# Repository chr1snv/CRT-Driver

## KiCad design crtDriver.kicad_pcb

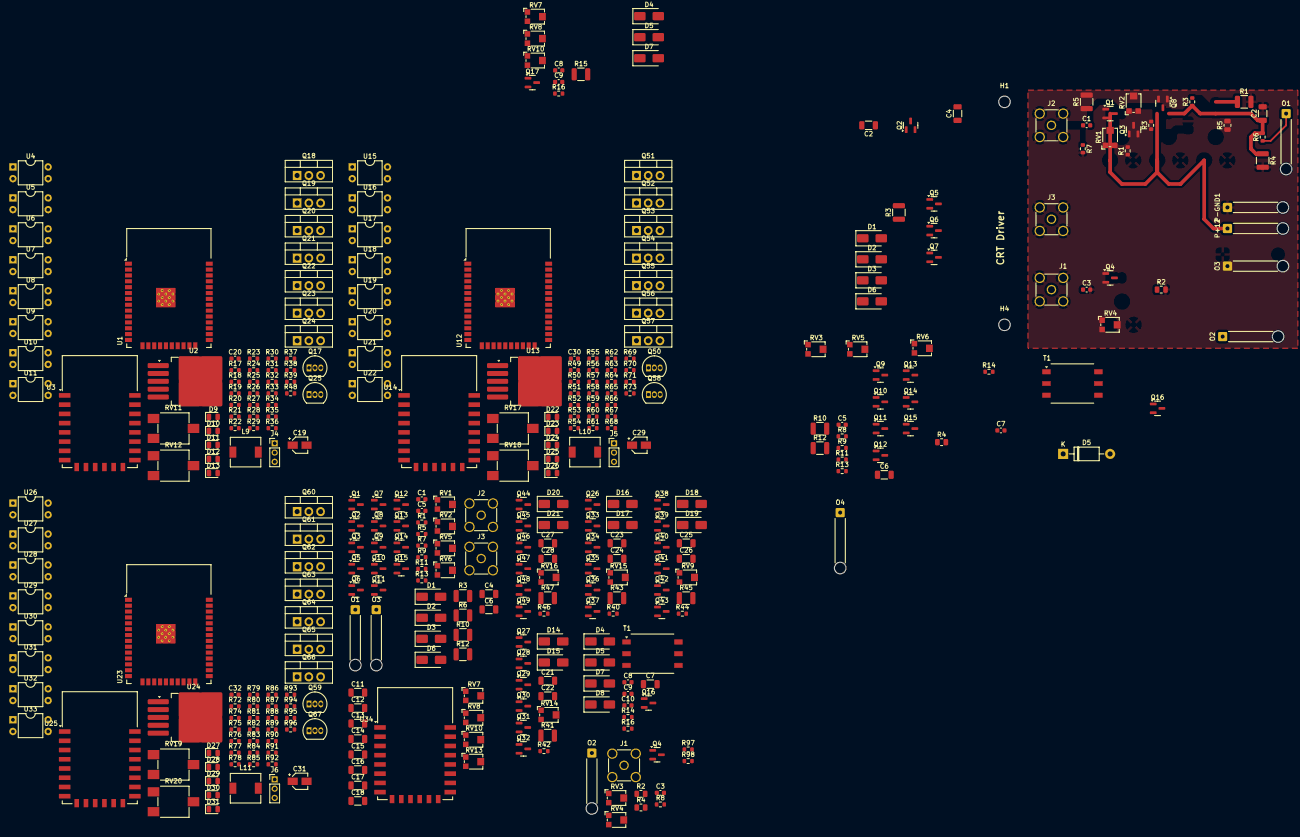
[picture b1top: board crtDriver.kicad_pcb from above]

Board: 2 copper layers, 372 parts (0 on the bottom side), 213 nets.

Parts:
C1, C1#2, C5, C5#2, C8: 4u; C_0603_1608Metric
C2, C4, C4#2, C6, C6#2, C21, C24, C26, C28: 47u; C_1206_3216Metric
C2#2: 2000u; C_1206_3216Metric
C3, C3#2: 100n; C_0603_1608Metric
C7, C8#2, C9#2, C10: 20u; C_0603_1608Metric
C7#2: 1000u; C_1206_3216Metric
C9: 1u; C_0603_1608Metric
C11, C12, C13, C14, C15, C16, C17, C18: 40u; C_1206_3216Metric
C19, C29, C31: 470uF 25V; CP_Elec_3x5.3
C20, C30, C32: 4.7uF 25V; C_0603_1608Metric
C22, C23, C25, C27: 1u; C_1206_3216Metric
D1, D1#2, D2, D2#2, D3, D3#2, D4, D4#2, D5, D5#3, D6, D6#2, D7, D7#2, D8, D14, D15, D16, D17, D18, D19, D20, D21: US1A; D_SMA
D5#2: 1N4007; D_DO-41_SOD81_P10.16mm_Horizontal
D9, D10, D11, D12, D13, D22, D23, D24, D25, D26, D27, D28, D29, D30, D31: 1N4001; D_0805_2012Metric
H1, H2, H3, H4: MountingHole; MountingHole_2.5mm
J1, J1#2: Lum_In; SMA_Amphenol_901-144_Vertical
J2, J2#2: H_Sync; SMA_Amphenol_901-144_Vertical
J3, J3#2: V_Sync; SMA_Amphenol_901-144_Vertical
J4, J5, J6: Conn_01x03_Female; PinHeader_1x03_P2.00mm_Vertical
L9, L10, L11: 9u; L_6.3x6.3_H3
O1, O1#2: H_Ramp_Out; SolderWire-0.25sqmm_1x01_D0.65mm_OD2mm_Relief
O2, O2#2: Lum_Out; SolderWire-0.25sqmm_1x01_D0.65mm_OD2mm_Relief
O3, O3#2, O4: V_Ramp_Out; SolderWire-0.25sqmm_1x01_D0.65mm_OD2mm_Relief
P+12: +12V; SolderWire-0.25sqmm_1x01_D0.65mm_OD2mm_Relief
P-GND1: +12V; SolderWire-0.25sqmm_1x01_D0.65mm_OD2mm_Relief
Q1, Q1#2, Q2, Q2#2, Q3, Q3#2, Q4, Q4#2, Q5, Q5#2, Q6, Q6#2, Q7, Q7#2, Q8, Q8#2, Q9, Q9#2, Q10, Q10#2, Q11, Q11#2, Q12, Q12#2, Q13, Q13#2, Q14, Q14#2, Q15, Q15#2, Q16#2, Q17, Q26, Q27, Q28, Q29, Q30, Q31, Q32, Q33, Q34, Q35, Q36, Q37, Q38, Q39, Q40, Q41, Q42, Q43, Q44, Q45, Q46, Q47, Q48, Q49: 2N7000; SOT-23
Q16: 410N; SOT-23
Q17#2, Q25, Q50, Q58, Q59, Q67: 2N7000; TO-92_Inline
Q18, Q19, Q20, Q21, Q22, Q23, Q24, Q51, Q52, Q53, Q54, Q55, Q56, Q57, Q60, Q61, Q62, Q63, Q64, Q65, Q66: IRF3205; TO-220-3_Vertical
R1, R3#4, R6, R12, R12#2, R41, R43, R45, R47: 10; R_1210_3225Metric
R1#2, R3, R5, R8, R8#2, R11, R11#2, R14, R40, R42, R44, R46: 10000; R_0603_1608Metric
R1#3, R7, R9, R9#2: 1000000; R_0603_1608Metric
R2, R2#2: 100000; R_0805_2012Metric
R3#2: 68; R_0603_1608Metric
R3#3, R5#3, R10, R10#2: 1000; R_1210_3225Metric
R4, R4#2: 100; R_0805_2012Metric
R4#3: 100; R_1210_3225Metric
R5#2: 1000; R_0805_2012Metric
R6#2, R7#2, R13, R13#2: 1000; R_0603_1608Metric
R14#2: 4; R_0603_1608Metric
R15: .5; R_1210_3225Metric
R16: 100000; R_0603_1608Metric
R16#2: .5; R_0603_1608Metric
R17, R24, R26, R27, R28, R29, R30, R39, R49, R56, R58, R59, R60, R61, R62, R71, R74, R81, R83, R84, R85, R86, R87, R96: 1K; R_0603_1608Metric
R18, R19, R20, R21, R22, R23, R50, R51, R52, R53, R54, R55, R75, R76, R77, R78, R79, R80: 200; R_0603_1608Metric
R25, R31, R32, R33, R34, R35, R36, R37, R38, R57, R63, R64, R65, R66, R67, R68, R69, R70, R82, R88, R89, R90, R91, R92, R93, R94, R95: 10K; R_0603_1608Metric
R48, R72, R73: 0; R_0603_1608Metric
R97, R98: 4.7K; R_0603_1608Metric
RV1, RV1#2, RV3#2, RV4, RV5, RV5#2, RV7#2, RV8, RV10#2, RV13: 2M; Potentiometer_Bourns_TC33X_Vertical
RV2, RV2#2, RV9, RV14, RV15, RV16: 250; Potentiometer_Bourns_TC33X_Vertical
RV3, RV4#2, RV7, RV8#2, RV10: 2000; Potentiometer_Bourns_TC33X_Vertical
RV6, RV6#2: 5000; Potentiometer_Bourns_TC33X_Vertical
RV11, RV17, RV19: 50K POT; Potentiometer_ACP_CA6-VSMD_Vertical
RV12, RV18, RV20: 2K POT; Potentiometer_ACP_CA6-VSMD_Vertical
T1: Transformer_1P_1S; Transformer_Wuerth_750315371
T1#2: Wuerth_750315371; Transformer_Wuerth_750315371
U1, U12, U23: ESP32-WROOM-32
U2, U13, U24: LM2576HVS-5; TO-263-5_TabPin3
U3, U14, U25, U34: ESP-12E
U4, U5, U6, U7, U8, U9, U10, U11, U15, U16, U17, U18, U19, U20, U21, U22, U26, U27, U28, U29, U30, U31, U32, U33: PC817; DIP-4_W7.62mm

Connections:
+3.3V: R97.1, R98.1
+5V: R48.2, R72.2, R73.2, RV12.3, RV18.3, RV20.3, U3.8 (VCC), U14.8 (VCC), U25.8 (VCC)
+12V: C2#2.1, C7#2.1, D4.1 (K), D7.1 (K), L9.2, L10.2, L11.2, P+12.1, Q2#2.1 (S), Q5.1 (S), Q8.1 (S), Q8#2.1 (S), Q12.1 (S), Q12#2.1 (S), Q15.1 (S), Q15#2.1 (S), Q19.2 (D), Q21.2 (D), Q23.2 (D), Q30.1 (S), Q32.1 (S), Q34.1 (S), Q37.1 (S), Q40.1 (S), Q43.1 (S), Q46.1 (S), Q49.1 (S), Q52.2 (D), Q54.2 (D), Q56.2 (D), Q61.2 (D), Q63.2 (D), Q65.2 (D), R1#2.1, R2.1, R2#2.1, R3#3.1, R4.1, R4#2.1, R5.1, R5#3.1, R10.1, R10#2.1, R11.1, R11#2.1, R15.2, R40.1, R42.1, R44.1, R46.1, RV1.1, RV1#2.1, RV3#2.1, RV4.1, RV5.1, RV5#2.1, RV10.1, T1.1 (AA), T1#2.1 (AA), U2.1 (VIN), U4.4, U13.1 (VIN), U15.4, U24.1 (VIN), U26.4
+36V: C19.1, C29.1, C31.1, D9.1 (K), D10.1 (K), D11.1 (K), D12.1 (K), D22.1 (K), D23.1 (K), D24.1 (K), D25.1 (K), D27.1 (K), D28.1 (K), D29.1 (K), D30.1 (K), R24.1, R26.1, R27.1, R28.1, R29.1, R30.1, R56.1, R58.1, R59.1, R60.1, R61.1, R62.1, R81.1, R83.1, R84.1, R85.1, R86.1, R87.1, RV11.3, RV17.3, RV19.3
/BLDC_Driver1/A: D23.2 (A), D26.2 (A), J5.1, Q52.3 (S), Q53.2 (D)
/BLDC_Driver1/ADC: R69.2, U14.2 (ADC)
/BLDC_Driver1/B: D24.2 (A), J5.2, Q56.3 (S), Q57.2 (D)
/BLDC_Driver1/C: D25.2 (A), J5.3, Q54.3 (S), Q55.2 (D)
/BLDC_Driver1/Flashing fails if high: U12.24 (IO2), U12.25 (IO0)
/BLDC_Driver2/A: D28.2 (A), D31.2 (A), J6.1, Q61.3 (S), Q62.2 (D)
/BLDC_Driver2/ADC: R94.2, U25.2 (ADC)
/BLDC_Driver2/B: D29.2 (A), J6.2, Q65.3 (S), Q66.2 (D)
/BLDC_Driver2/C: D30.2 (A), J6.3, Q63.3 (S), Q64.2 (D)
/BLDC_Driver2/Flashing fails if high: U23.24 (IO2), U23.25 (IO0)
/BLDC_Driver/A: D10.2 (A), D13.2 (A), J4.1, Q19.3 (S), Q20.2 (D)
/BLDC_Driver/ADC: R37.2, U3.2 (ADC)
/BLDC_Driver/B: D11.2 (A), J4.2, Q23.3 (S), Q24.2 (D)
/BLDC_Driver/C: D12.2 (A), J4.3, Q21.3 (S), Q22.2 (D)
/BLDC_Driver/Flashing fails if high: U1.24 (IO2), U1.25 (IO0)
/BLDC_Driver/SCL: R98.2, U1.22 (SDI/SD1), U12.22 (SDI/SD1), U23.22 (SDI/SD1)
/BLDC_Driver/SDA: R97.2, U1.21 (SDO/SD0), U12.21 (SDO/SD0), U23.21 (SDO/SD0)
/FocusingCoils/PWMAmplifier1/SELECTED_RAMP_OUT: C13.1, C14.1, C24.2, D17.1 (K), Q35.1 (S), RV13.1
/FocusingCoils/PWMAmplifier1/Scaled_Ramp_IN: C23.1, Q26.2 (G), Q34.2 (G), RV13.2
/FocusingCoils/PWMAmplifier2/SELECTED_RAMP_OUT: C15.1, C16.1, C26.2, D19.1 (K), Q41.1 (S), RV8.1
/FocusingCoils/PWMAmplifier2/Scaled_Ramp_IN: C25.1, Q38.2 (G), Q40.2 (G), RV8.2
/FocusingCoils/PWMAmplifier3/SELECTED_RAMP_OUT: C17.1, C18.1, C28.2, D21.1 (K), Q47.1 (S), RV10#2.1
/FocusingCoils/PWMAmplifier3/Scaled_Ramp_IN: C27.1, Q44.2 (G), Q46.2 (G), RV10#2.2
/FocusingCoils/PWMAmplifier/SELECTED_RAMP_OUT: C11.1, C12.1, C21.2, D15.1 (K), Q28.1 (S), RV7#2.1
/FocusingCoils/PWMAmplifier/Scaled_Ramp_IN: C22.1, Q29.2 (G), Q30.2 (G), RV7#2.2
/HighVoltageAndFillamentPower/H_Sync_Toggle: Q2.1 (S), Q7.2 (G), Q8#2.2 (G), Q16.2 (G), R5.2
/HorizontalAndVerticalRamp/H_Ramp_Out: C4.2, D6.1 (K), Q6#2.1 (S), R7#2.2
/HorizontalAndVerticalRamp/H_Sync: C1#2.1, J2.1 (In), R1#3.1
/HorizontalAndVerticalRamp/Inverted_H_Sync: Q1#2.1 (S), Q2.2 (G), Q5.2 (G), R3#3.2
/HorizontalAndVerticalRamp/Inverted_V_Sync: Q9#2.1 (S), Q10#2.2 (G), Q12#2.2 (G), R10.2
/HorizontalAndVerticalRamp/Positive_V_Sync: Q10#2.1 (S), Q14#2.2 (G), Q15#2.2 (G), R11.2
/HorizontalAndVerticalRamp/V_Ramp_Out: C6#2.2, D3.1 (K), Q13.1 (S), R13#2.2
/HorizontalAndVerticalRamp/V_Sync: C5#2.1, J3#2.1 (In), R9#2.1
/Inverted H Sync: Q1.1 (S), Q3.2 (G), Q8.2 (G), R5#3.2
/Inverted V Sync: Q9.1 (S), Q10.2 (G), R10#2.2
/Positive H Sync: Q2#2.2 (G), Q3.1 (S), Q5#2.2 (G), R1#2.2
/Positive V Sync: Q10.1 (S), Q14.2 (G), Q15.2 (G), R11#2.2
GND: C2.2, C2#2.2, C7.2, C7#2.2, C8#2.2, C11.2, C12.2, C13.2, C14.2, C15.2, C16.2, C17.2, C18.2, C19.2, C20.2, C22.2, C23.2, C25.2, C27.2, C29.2, C30.2, C31.2, C32.2, D5.2 (A), J1.2 (Ext), J1#2.2 (Ext), J2.2 (Ext), J2#2.2 (Ext), J3.2 (Ext), J3#2.2 (Ext), O3.1, P-GND1.1, Q1.3 (D), Q1#2.3 (D), Q2.3 (D), Q3.3 (D), Q3#2.3 (D), Q4.3 (D), Q4#2.3 (D), Q5#2.3 (D), Q6.3 (D), Q6#2.3 (D), Q7.3 (D), Q7#2.3 (D), Q9.3 (D), Q9#2.3 (D), Q10.3 (D), Q10#2.3 (D), Q11.3 (D), Q11#2.3 (D), Q13.3 (D), Q13#2.3 (D), Q14.3 (D), Q14#2.3 (D), Q17.3 (D), Q18.3 (S), Q20.3 (S), Q22.3 (S), Q24.3 (S), Q25.3 (D), Q26.3 (D), Q27.3 (D), Q28.3 (D), Q29.3 (D), Q31.3 (D), Q33.3 (D), Q35.3 (D), Q36.3 (D), Q38.3 (D), Q39.3 (D), Q41.3 (D), Q42.3 (D), Q44.3 (D), Q45.3 (D), Q47.3 (D), Q48.3 (D), Q51.3 (S), Q53.3 (S), Q55.3 (S), Q57.3 (S), Q58.3 (D), Q60.3 (S), Q62.3 (S), Q64.3 (S), Q66.3 (S), Q67.3 (D), R1.2, R1#3.2, R4#3.2, R5#2.2, R7.2, R9.2, R9#2.2, R14.2, R14#2.2, R16.2, R16#2.2, R17.1, R18.1, R19.1, R20.1, R21.1, R22.1, R23.1, R25.1, R31.2, R32.2, R33.2, R34.2, R35.2, R36.2, R39.2, R49.1, R50.1, R51.1, R52.1, R53.1, R54.1, R55.1, R57.1, R63.2, R64.2, R65.2, R66.2, R67.2, R68.2, R71.2, R74.1, R75.1, R76.1, R77.1, R78.1, R79.1, R80.1, R82.1, R88.2, R89.2, R90.2, R91.2, R92.2, R93.2, R96.2, RV1.3, RV1#2.3, RV3#2.3, RV4.3, RV5.3, RV5#2.3, RV7#2.3, RV8.3, RV8#2.3, RV10.3, RV10#2.3, RV11.1, RV12.1, RV13.3, RV17.1, RV18.1, RV19.1, RV20.1, T1.3 (SA), T1#2.3 (SA), U1.1 (GND), U1.15 (GND), U1.38 (GND), U1.39 (GND), U2.3 (GND), U3.15 (GND), U5.2, U5.3, U12.1 (GND), U12.15 (GND), U12.38 (GND), U12.39 (GND), U13.3 (GND), U14.15 (GND), U16.2, U16.3, U23.1 (GND), U23.15 (GND), U23.38 (GND), U23.39 (GND), U24.3 (GND), U25.15 (GND), U27.2, U27.3, U34.15 (GND)
unnamed: C8.1, RV7.2
unnamed: D1.2 (A), D1#2.2 (A), Q2#2.3 (D), Q5.3 (D), RV2.1
unnamed: C4.1, C4#2.2, C9.1, D1.1 (K), D1#2.1 (K), Q7.1 (S), Q7#2.1 (S), R6#2.2
unnamed: D2.2 (A), D2#2.2 (A), Q12.3 (D), Q12#2.3 (D), RV6.1, RV6#2.1
unnamed: C6.1, C6#2.1, D2.1 (K), D2#2.1 (K), Q14.1 (S), Q14#2.1 (S)
unnamed: D3.2 (A), D3#2.2 (A), Q15.3 (D), Q15#2.3 (D)
unnamed: C6.2, D3#2.1 (K), Q13#2.1 (S), R13.2
unnamed: D4.2 (A), D4#2.2 (A), D5.1 (K), Q16.1 (S), T1.4 (SB), T1#2.2 (AB)
unnamed: C7.1, D4#2.1 (K)
unnamed: D5#2.2 (A), D5#3.2 (A), T1#2.4 (SB)
unnamed: C8#2.1, C9#2.1, D5#2.1 (K), D5#3.1 (K), D7#2.2 (A)
unnamed: D6.2 (A), D6#2.2 (A), Q8.3 (D), Q8#2.3 (D), RV2#2.1
unnamed: C4#2.1, D6#2.1 (K), Q5#2.1 (S)
unnamed: D7.2 (A), Q16#2.1 (S), T1.2 (AB)
unnamed: C9#2.2, C10.1, D7#2.1 (K), D8.2 (A)
unnamed: C10.2, D8.1 (K), R16.1
unnamed: D9.2 (A), L9.1, Q18.2 (D)
unnamed: C20.1, D13.1 (K), Q25.1 (S), R38.1
unnamed: D14.2 (A), Q30.3 (D), RV14.1
unnamed: C21.1, D14.1 (K), Q31.1 (S)
unnamed: D15.2 (A), Q32.3 (D)
unnamed: D16.2 (A), Q34.3 (D), RV15.1
unnamed: C24.1, D16.1 (K), Q36.1 (S)
unnamed: D17.2 (A), Q37.3 (D)
unnamed: D18.2 (A), Q40.3 (D), RV9.1
unnamed: C26.1, D18.1 (K), Q42.1 (S)
unnamed: D19.2 (A), Q43.3 (D)
unnamed: D20.2 (A), Q46.3 (D), RV16.1
unnamed: C28.1, D20.1 (K), Q48.1 (S)
unnamed: D21.2 (A), Q49.3 (D)
unnamed: D22.2 (A), L10.1, Q51.2 (D)
unnamed: C30.1, D26.1 (K), Q58.1 (S), R70.1
unnamed: D27.2 (A), L11.1, Q60.2 (D)
unnamed: C32.1, D31.1 (K), Q67.1 (S), R95.1
unnamed: C3.1, C3#2.1, J1.1 (In), J1#2.1 (In)
unnamed: C1.1, J2#2.1 (In), R7.1
unnamed: C5.1, J3.1 (In), R9.1
unnamed: O1.1, O1#2.1, R6#2.1, R7#2.1
unnamed: O2.1, O2#2.1, R8.1, R8#2.1
unnamed: O3#2.1, R13#2.1
unnamed: O4.1, R13.1
unnamed: C1.2, C1#2.2, Q1.2 (G), Q1#2.2 (G), RV1.2, RV1#2.2
unnamed: C2.1, R3.1, R4#3.1
unnamed: Q3#2.1 (S), Q3#2.2 (G), Q6#2.2 (G), R3.2, R6.2
unnamed: C3.2, C3#2.2, Q4.2 (G), Q4#2.2 (G), RV3#2.2, RV4.2
unnamed: Q4.1 (S), Q4#2.1 (S), R8.2, R8#2.2, RV3.2, RV4#2.2
unnamed: Q6.1 (S), Q6.2 (G), Q7#2.2 (G), R3#2.2, R3#4.2
unnamed: C5.2, C5#2.2, Q9.2 (G), Q9#2.2 (G), RV5.2, RV5#2.2
unnamed: Q11.1 (S), Q11.2 (G), Q11#2.1 (S), Q11#2.2 (G), Q13.2 (G), Q13#2.2 (G), R12.2, R12#2.2
unnamed: Q16.3 (D), Q16#2.3 (D), R14#2.1, R16#2.1
unnamed: C9.2, Q16#2.2 (G)
unnamed: Q17#2.3 (D), RV12.2
unnamed: C8.2, Q17.2 (G), Q17#2.2 (G), RV11.2
unnamed: Q17.1 (S), Q17#2.1 (S), RV8#2.1, RV10.2, U5.1
unnamed: Q18.1 (G), R25.2, U4.3
unnamed: Q19.1 (G), R33.1, U6.3
unnamed: Q20.1 (G), R34.1, U7.3
unnamed: Q21.1 (G), R35.1, U10.3
unnamed: Q22.1 (G), R36.1, U11.3
unnamed: Q23.1 (G), R31.1, U8.3
unnamed: Q24.1 (G), R32.1, U9.3
unnamed: Q25.2 (G), U3.21 (GPIO3/RXD)
unnamed: Q26.1 (S), Q36.2 (G), Q37.2 (G), R40.2
unnamed: Q27.1 (S), Q27.2 (G), Q28.2 (G), R41.2
unnamed: Q29.1 (S), Q31.2 (G), Q32.2 (G), R42.2
unnamed: Q33.1 (S), Q33.2 (G), Q35.2 (G), R43.2
unnamed: Q38.1 (S), Q42.2 (G), Q43.2 (G), R44.2
unnamed: Q39.1 (S), Q39.2 (G), Q41.2 (G), R45.2
unnamed: Q44.1 (S), Q48.2 (G), Q49.2 (G), R46.2
unnamed: Q45.1 (S), Q45.2 (G), Q47.2 (G), R47.2
unnamed: Q50.3 (D), RV18.2
unnamed: Q50.2 (G), RV17.2
unnamed: Q50.1 (S), U16.1
unnamed: Q51.1 (G), R57.2, U15.3
unnamed: Q52.1 (G), R65.1, U17.3
unnamed: Q53.1 (G), R66.1, U18.3
unnamed: Q54.1 (G), R67.1, U21.3
unnamed: Q55.1 (G), R68.1, U22.3
unnamed: Q56.1 (G), R63.1, U19.3
unnamed: Q57.1 (G), R64.1, U20.3
unnamed: Q58.2 (G), U14.21 (GPIO3/RXD)
unnamed: Q59.3 (D), RV20.2
unnamed: Q59.2 (G), RV19.2
unnamed: Q59.1 (S), U27.1
unnamed: Q60.1 (G), R82.2, U26.3
unnamed: Q61.1 (G), R90.1, U28.3
unnamed: Q62.1 (G), R91.1, U29.3
unnamed: Q63.1 (G), R92.1, U32.3
unnamed: Q64.1 (G), R93.1, U33.3
unnamed: Q65.1 (G), R88.1, U30.3
unnamed: Q66.1 (G), R89.1, U31.3
unnamed: Q67.2 (G), U25.21 (GPIO3/RXD)
unnamed: R2.2, R2#2.2, RV3.3, RV4#2.3
unnamed: R3#4.1, RV2#2.2
unnamed: R4.2, R4#2.2, RV3.1, RV4#2.1
unnamed: R6.1, RV2.2
unnamed: R12.1, R12#2.1, RV6.2, RV6#2.2
unnamed: R17.2, U4.2
unnamed: R18.2, U7.2
unnamed: R19.2, U8.2
unnamed: R20.2, U9.2
unnamed: R21.2, U10.2
unnamed: R22.2, U11.2
unnamed: R23.2, U6.2
unnamed: R24.2, U9.4
unnamed: R26.2, U6.4
unnamed: R27.2, U7.4
unnamed: R28.2, U8.4
unnamed: R29.2, U10.4
unnamed: R30.2, U11.4
unnamed: R37.1, R38.2, R39.1
unnamed: R41.1, RV14.2
unnamed: R43.1, RV15.2
unnamed: R45.1, RV9.2
unnamed: R47.1, RV16.2
unnamed: R49.2, U15.2
unnamed: R50.2, U18.2
unnamed: R51.2, U19.2
unnamed: R52.2, U20.2
unnamed: R53.2, U21.2
unnamed: R54.2, U22.2
unnamed: R55.2, U17.2
unnamed: R56.2, U20.4
unnamed: R58.2, U17.4
unnamed: R59.2, U18.4
unnamed: R60.2, U19.4
unnamed: R61.2, U21.4
unnamed: R62.2, U22.4
unnamed: R69.1, R70.2, R71.1
unnamed: R74.2, U26.2
unnamed: R75.2, U29.2
unnamed: R76.2, U30.2
unnamed: R77.2, U31.2
unnamed: R78.2, U32.2
unnamed: R79.2, U33.2
unnamed: R80.2, U28.2
unnamed: R81.2, U31.4
unnamed: R83.2, U28.4
unnamed: R84.2, U29.4
unnamed: R85.2, U30.4
unnamed: R86.2, U32.4
unnamed: R87.2, U33.4
unnamed: R94.1, R95.2, R96.1
unnamed: RV7.3, RV8#2.2
unnamed: R48.1, U2.2 (OUT)
unnamed: U3.17 (GPIO2), U5.4
unnamed: U3.19 (GPIO4), U7.1
unnamed: U3.20 (GPIO5), U4.1
unnamed: U3.6 (GPIO12), U9.1
unnamed: U3.7 (GPIO13), U10.1
unnamed: U3.5 (GPIO14), U8.1
unnamed: U3.16 (GPIO15), U6.1
unnamed: U3.4 (GPIO16), U11.1
unnamed: R73.1, U13.2 (OUT)
unnamed: U14.17 (GPIO2), U16.4
unnamed: U14.19 (GPIO4), U18.1
unnamed: U14.20 (GPIO5), U15.1
unnamed: U14.6 (GPIO12), U20.1
unnamed: U14.7 (GPIO13), U21.1
unnamed: U14.5 (GPIO14), U19.1
unnamed: U14.16 (GPIO15), U17.1
unnamed: U14.4 (GPIO16), U22.1
unnamed: R72.1, U24.2 (OUT)
unnamed: U25.17 (GPIO2), U27.4
unnamed: U25.19 (GPIO4), U29.1
unnamed: U25.20 (GPIO5), U26.1
unnamed: U25.6 (GPIO12), U31.1
unnamed: U25.7 (GPIO13), U32.1
unnamed: U25.5 (GPIO14), U30.1
unnamed: U25.16 (GPIO15), U28.1
unnamed: U25.4 (GPIO16), U33.1

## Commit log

2024-10-10 initial commit of crt driver kicad files
2024-10-11 got potentiometer parameters to show in ui, got spice simulation to run
2024-10-11 got spice simulation to run with +V, v sync input. added 2n7000 model and fixed potentiometer model pinout
2024-10-12 added 3d model for potentiometer, started on component placement and trace routing
2024-10-13 changed circuit to use 2n7000's as low side switches/valves to get voltage gain, started on current mirror for linear capacitor voltage ramp (it also will likely only work on the low side maybe requi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
2024-10-14 changed design to have a current mirror constant current drain for output capacitor and added components to improve performance of it
2024-10-14 duplicated v sync section for h sync, adjusted luminosity amplifier passive component values
2024-10-18 updated schematic with voltage booster section, haven't found settings for it to be simulated stabily in spice without many iterations/timesteps yet
2024-10-20 updated to kicad 8, simulation for flyback runs though uses 10gb ram or so for 20ms of simulation with 0.01e-03 seconds ish timestep
2024-10-22 changed to hierarchical schematic sheets for electron microscope components (pump motor controllers, focusing coils, etc)
2024-10-23 added more untested ideas for schematics
2024-10-23 linked models so spice simulation runs
2024-10-24 added new spice directives to improve simulation speed, added sections for motor drivers, micro controlers, i2c bus connections, realized that focusing coils, hv, horizontal and vertical ramp will ne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
2024-11-10 changed bldc driver schematic to use esp32 devkit
2025-06-20 added sections to add to overview schematic, added some of the component schematics
2025-06-20 added more labels of components to top level schematic
